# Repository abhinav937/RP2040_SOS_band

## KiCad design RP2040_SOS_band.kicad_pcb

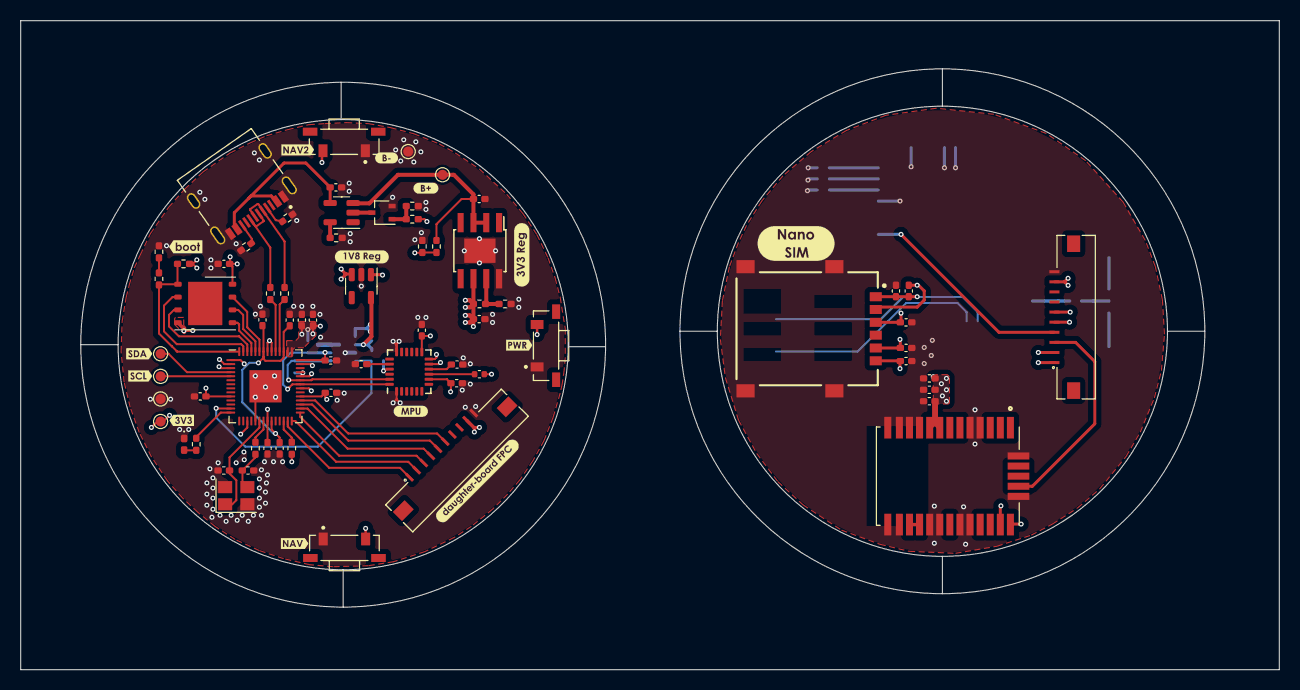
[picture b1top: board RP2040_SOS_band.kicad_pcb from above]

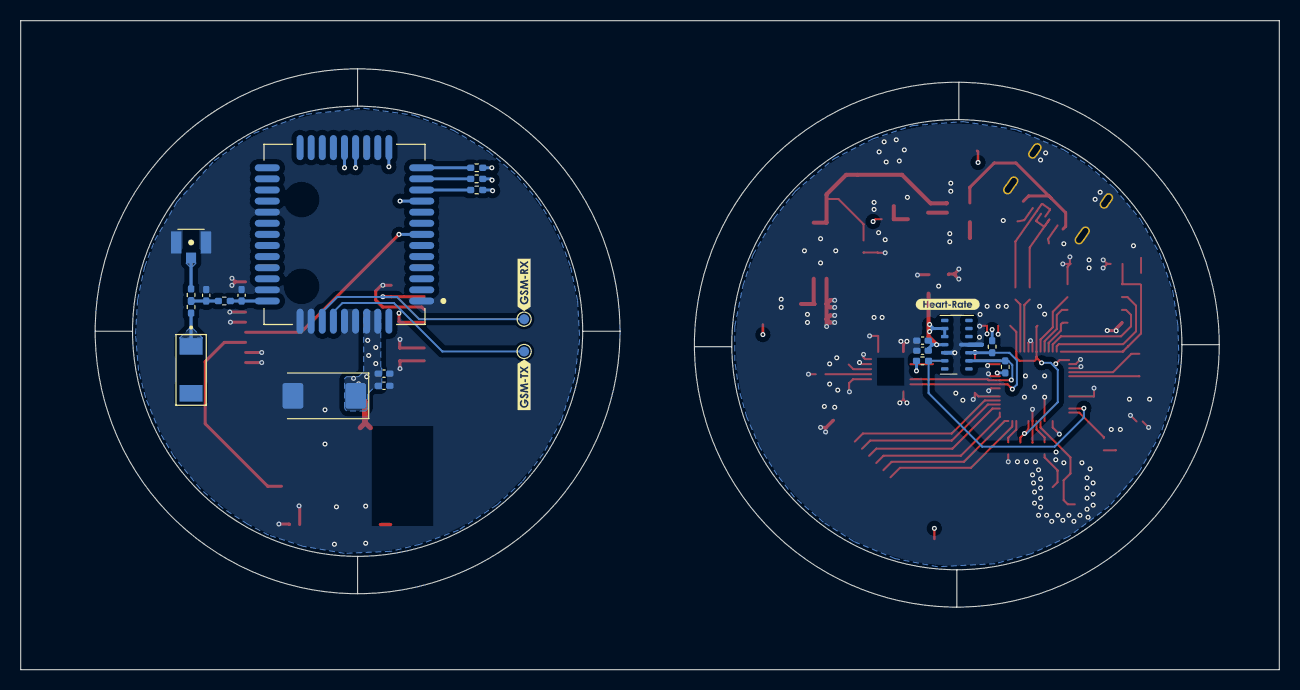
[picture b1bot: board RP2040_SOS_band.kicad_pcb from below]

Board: 4 copper layers, 124.7 x 64.3 mm, 107 parts (25 on the bottom side), 71 nets.

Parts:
C1, C2, C3, C4, C5, C6, C7, C8, C9, C12, C21, C22, C23, C36: 10uF; C_0402_1005Metric_Pad0.74x0.62mm_HandSolder
C10, C16, C18, C19, C20: 0.1uF; C_0402_1005Metric_Pad0.74x0.62mm_HandSolder
C11: 10pF; C_0402_1005Metric_Pad0.74x0.62mm_HandSolder
C13, C14: 27pF; C_0402_1005Metric_Pad0.74x0.62mm_HandSolder
C15: 100pF; C_0402_1005Metric_Pad0.74x0.62mm_HandSolder
C17: 2.2nF; C_0402_1005Metric_Pad0.74x0.62mm_HandSolder
C24, C25, C26, C27, C31: 30pF; C_0402_1005Metric_Pad0.74x0.62mm_HandSolder
C28, C30: 100nF; C_0402_1005Metric_Pad0.74x0.62mm_HandSolder
C29: 470uF; CP_EIA-7343-30_AVX-N
C32, C33: NC; C_0402_1005Metric_Pad0.74x0.62mm_HandSolder
D1: RED; LED_0402_1005Metric_Pad0.77x0.64mm_HandSolder
E1: NN02-201; XCVR_NN02-201
J1: TYPE_C-31M12; HRO_TYPE-C-31-M-12
J2: SIM8060-6-0-14-00-A; GCT_SIM8060-6-0-14-00-A
J3: 10Pin FPC TOP Board; 686110183522
J4: 10Pin FPC Bottom board; 686110183522
J5: U.FL-R-SMT-1(10); HRS_U.FL-R-SMT-1(10)
JP1: I2C address change; C_0402_1005Metric
Q1: BSS214; SOT-323_SC-70
R1, R2: 27; R_0402_1005Metric_Pad0.72x0.64mm_HandSolder
R3, R4, R7, R19: 1k; R_0402_1005Metric_Pad0.72x0.64mm_HandSolder
R5, R9, R13, R18: 10k; R_0402_1005Metric_Pad0.72x0.64mm_HandSolder
R6, R8, R14, R15, R16: 5.1k; R_0402_1005Metric_Pad0.72x0.64mm_HandSolder
R10: 2.2k; R_0402_1005Metric_Pad0.72x0.64mm_HandSolder
R11: DNP/TP; R_0402_1005Metric_Pad0.72x0.64mm_HandSolder
R12, R23, R24: 0; R_0402_1005Metric_Pad0.72x0.64mm_HandSolder
R17: 27k; R_0402_1005Metric_Pad0.72x0.64mm_HandSolder
R20, R21, R22: 22; R_0402_1005Metric_Pad0.72x0.64mm_HandSolder
R25: 162k 1%; R_0402_1005Metric_Pad0.72x0.64mm_HandSolder
R26: 30.1k 1%; R_0402_1005Metric_Pad0.72x0.64mm_HandSolder
SW1: NAV2; SW_TL3330AF260QG
SW2: PWR; SW_TL3330AF260QG
SW3: NAV; SW_TL3330AF260QG
TP1: RXD; TestPoint_Pad_D1.0mm
TP2: TXD; TestPoint_Pad_D1.0mm
TP3: 3.3; TestPoint_Pad_D1.0mm
TP4: SDA; TestPoint_Pad_D1.0mm
TP5: SCL; TestPoint_Pad_D1.0mm
TP6: GND; TestPoint_Pad_D1.0mm
TP7: Bat+; TestPoint_Pad_D1.0mm
TP8: Bat-; TestPoint_Pad_D1.0mm
U1: RP2040; QFN-56-1EP_7x7mm_P0.4mm_EP3.2x3.2mm
U2: TPS7A7001DDA; TI_SO-PowerPAD-8
U3: W25Q32JVSS; WSON-8-1EP_6x5mm_P1.27mm_EP3.4x4.3mm
U4: MAX30102; Maxim_OLGA-14_3.3x5.6mm_P0.8mm
U5: MCP73831-2-OT; SOT-23-5
U6: MPU-6050; InvenSense_QFN-24_4x4mm_P0.5mm
U7: AP2127K-1.8; SOT-23-5
U8: L96; XCVR_L96
U10: M66; XCVR_M66
Y1: Crystal_GND24; Crystal_SMD_3225-4Pin_3.2x2.5mm
kibuzzard-648D8F43: G***; kibuzzard-648D8F43
kibuzzard-648D8F93: G***; kibuzzard-648D8F93
kibuzzard-648D8FB3: G***; kibuzzard-648D8FB3
kibuzzard-648D8FC5: G***; kibuzzard-648D8FC5
kibuzzard-648D90C6: G***; kibuzzard-648D90C6
kibuzzard-648D90E2: G***; kibuzzard-648D90E2
kibuzzard-648D91AF: G***; kibuzzard-648D91AF
kibuzzard-648D92FA: G***; kibuzzard-648D92FA
kibuzzard-648D902E: G***; kibuzzard-648D902E
kibuzzard-648D909E: G***; kibuzzard-648D909E
kibuzzard-648D920B: G***; kibuzzard-648D920B
kibuzzard-648D921A: G***; kibuzzard-648D921A
kibuzzard-648D944C: G***; kibuzzard-648D944C
kibuzzard-648D9126: G***; kibuzzard-648D9126
kibuzzard-648D9334: G***; kibuzzard-648D9334
kibuzzard-648D9374: G***; kibuzzard-648D9374
kibuzzard-648D9446: G***; kibuzzard-648D9446

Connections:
+1V1: C7.1, C8.1, C9.1, U1.23 (DVDD), U1.45 (VREG_VOUT), U1.50 (DVDD)
+1V8: C20.1, C21.1, U4.11 (VDD), U7.5 (VOUT)
+BATT: C23.1, R13.1, TP7.1, U2.2 (EN), U2.3 (IN), U5.3 (V_{BAT})
/RP2040/QSPI_CS: R4.2, R5.2, U1.56 (QSPI_SS), U3.1 (~CS)
/RP2040/QSPI_SCLK: U1.52 (QSPI_SCLK), U3.6 (CLK)
/RP2040/QSPI_SD0: U1.53 (QSPI_SD0), U3.5 (DI(IO0))
/RP2040/QSPI_SD1: U1.55 (QSPI_SD1), U3.2 (DO(IO1))
/RP2040/QSPI_SD2: U1.54 (QSPI_SD2), U3.3 (IO2)
/RP2040/QSPI_SD3: U1.51 (QSPI_SD3), U3.7 (IO3)
/RP2040/RUN: R3.2, U1.26 (RUN)
/RP2040/USB_N: R2.2, U1.46 (USB_DM)
/RP2040/USB_P: R1.2, U1.47 (USB_DP)
/quectel m66/SIM_CLK: R21.1, U10.13 (SIM_CLK)
/quectel m66/SIM_GND: C28.2, J2.C5 (GND), U10.10 (SIM_GND)
/quectel m66/SIM_IO: R22.1, U10.11 (SIM_DATA)
/quectel m66/SIM_RST: R20.1, U10.12 (SIM_RST)
/quectel m66/SIM_VDD: C27.1, C28.1, J2.C1 (VCC), U10.14 (SIM_VDD)
CHARGER_EN: R18.1, U1.38 (GPIO26_ADC0)
D+: J1.A6 (DP1), J1.B6 (DP2), R1.1
D-: J1.A7 (DN1), J1.B7 (DN2), R2.1
Force_ON: J3.3, U1.29 (GPIO18)
Force_ON_t: J4.3, U8.28 (FORCE_ON)
GND: C1.2, C2.2, C3.2, C4.2, C5.2, C6.2, C7.2, C8.2, C9.2, C10.2, C11.2, C12.2, C13.2, C14.2, C15.2, C16.2, C17.2, C18.2, C19.2, C20.2, C21.2, C22.1, C23.2, C24.2, C25.2, C26.2, C27.2, C29.2, C30.2, C31.2, C32.2, C33.2, C36.2, D1.1 (K), J1.A1_B12 (GND), J1.B1_A12 (GND), J1.S1 (SHIELD), J1.S2 (SHIELD), J1.S3 (SHIELD), J1.S4 (SHIELD), J2.S1 (SHIELD), J2.S2 (SHIELD), J2.S3 (SHIELD), J2.S4 (SHIELD), J3.10, J4.10, J5.1 (GND), J5.3 (GND), Q1.2 (S), R6.1, R8.2, R10.1, R11.1, R17.2, R19.1, R26.2, SW1.1, SW2.1, SW3.1, TP6.1, TP8.1, U1.19 (TESTEN), U1.57 (GND), U2.8 (GND), U2.9 (EP), U3.4 (GND), U4.4 (PGND), U4.12 (GND), U6.1 (CLKIN), U6.11 (FSYNC), U6.18 (GND), U7.2 (GND), U8.4 (GND), U8.5 (GND), U8.10 (GND), U8.11 (GND), U8.12 (GND), U8.13 (GND), U8.14 (GND), U8.15 (GND), U8.18 (GND), U8.19 (GND), U8.21 (GND), U8.22 (GND), U8.27 (GND), U8.31 (GND), U10.1 (AGND), U10.27 (GND), U10.34 (GND), U10.36 (GND), U10.37 (GND), U10.40 (GND), U10.41 (GND), Y1.2, Y1.4
GPS_RXD: J3.5, U1.31 (GPIO20)
GPS_RXD_t: J4.5, U8.26 (RXD1)
GPS_TXD: J3.6, U1.32 (GPIO21)
GPS_TXD_t: J4.6, U8.25 (TXD1)
GSM_RX: J3.1, U1.27 (GPIO16)
GSM_RX_t: J4.1, U10.18 (RXD)
GSM_TX: J3.2, U1.28 (GPIO17)
GSM_TX_t: J4.2, U10.17 (TXD)
Heart_rate_INT: R14.1, U1.13 (GPIO10), U4.13 (~INT)
MAX30102_SCL: R16.2, U1.37 (GPIO25), U4.2 (SCL), U6.23 (SCL)
MAX30102_SDA: R15.2, U1.36 (GPIO24), U4.3 (SDA), U6.24 (SDA)
MPU_INT: U1.35 (GPIO23), U6.12 (INT)
NAV_BUTTON: SW3.2, U1.17 (GPIO14)
NAV_BUTTON_2: SW1.2, U1.2 (GPIO0)
unnamed: C14.1, R7.1, Y1.3
unnamed: C32.1, R12.1, R23.2, R24.1
unnamed: D1.2 (A), R9.1
unnamed: E1.1, R24.2
unnamed: J1.A5 (CC1), R8.1
unnamed: J1.B5 (CC2), R6.2
unnamed: C24.1, J2.C3 (CLK), R21.2
unnamed: C25.1, J2.C7 (IO), R22.2
unnamed: C26.1, J2.C2 (RST), R20.2
unnamed: J5.2 (SIG), R12.2
unnamed: JP1.2 (B), U6.9 (AD0)
unnamed: Q1.3 (D), U5.2 (V_{SS})
unnamed: Q1.1 (G), R18.2, R19.2
unnamed: R4.1, R11.2
unnamed: R25.2, R26.1, U2.7 (FB)
unnamed: R10.2, U5.5 (PROG)
unnamed: C17.1, U6.20 (CPOUT)
unnamed: C19.1, U6.10 (REGOUT)
unnamed: U8.16 (RF_OUT), U8.17 (RF_IN)
unnamed: TP1.1, U10.38 (DBG_RXD)
unnamed: TP2.1, U10.39 (DBG_TXD)
unnamed: C33.1, R23.1, U10.35 (RF_ANT)
Onboard_LED: R9.2, U1.14 (GPIO11)
PWR_BUTTON: SW2.2, U1.3 (GPIO1)
PWR_KEY_GSM: J3.4, U1.30 (GPIO19)
PWR_KEY_GSM_t: J4.4, U10.7 (PWRKEY)
SCL_OLED: TP5.1, U1.5 (GPIO3)
SDA_OLED: TP4.1, U1.4 (GPIO2)
VBUS: C22.2, J1.A4_B9 (VBUS), J1.B4_A9 (VBUS), U5.4 (V_{DD})
VDD_3.3: C1.1, C2.1, C3.1, C4.1, C5.1, C6.1, C12.1, C16.1, C18.1, C36.1, J3.9, JP1.1 (A), R3.1, R5.1, R14.2, R15.1, R16.1, R25.1, TP3.1, U1.1 (IOVDD), U1.10 (IOVDD), U1.22 (IOVDD), U1.33 (IOVDD), U1.42 (IOVDD), U1.43 (ADC_AVDD), U1.44 (VREG_IN), U1.48 (USB_VDD), U1.49 (IOVDD), U2.6 (OUT), U3.8 (VCC), U4.9 (VLED+), U4.10 (VLED+), U6.8 (VLOGIC), U6.13 (VDD), U7.1 (VIN), U7.3 (EN)
VDD_3.3_t: C10.1, C11.1, C15.1, C29.1, C30.1, C31.1, J4.9, U8.8 (V_BCKP), U8.9 (VCC), U10.42 (VBAT), U10.43 (VBAT)
V_SENSE: R13.2, R17.1, U1.41 (GPIO29_ADC3)
XIN: C13.1, U1.20 (XIN), Y1.1
XOUT: R7.2, U1.21 (XOUT)

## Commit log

2023-05-12 created files
2023-05-12 added rp2040 and it's subcircuits in schematic
2023-05-16 almost final schematic
2023-05-19 assigned footprints and checked the schematic
2023-06-15 bottom board conn. done
2023-07-13 Final Design
2023-10-26 Create LICENSE
